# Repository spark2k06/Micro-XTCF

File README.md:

Micro XTCF (Very Low Profile) Rev1.0 ReadMe
----------------------------

8-bit ISA CompactFlash interface + Boot ROM (two separate functions that can be used individually).

Credit:
-------

Design uses schematic from Monotech-PC, which, in turn, is based on the schematic from XT-IDE Rev2 and Glitchworks:

https://github.com/monotech/XT-IDE-Deluxe
http://www.github.com/glitchwrks/xt_ide

XT-IDE Universal BIOS\
www.xtideuniversalbios.org  
www.xtideuniversalbios.org/binaries  

Use the latest working binary that includes XTIDECFG.COM (config utility), ide_xt.bin (8086/8088), ide_xtp.bin (80186/V20/V30 and up).

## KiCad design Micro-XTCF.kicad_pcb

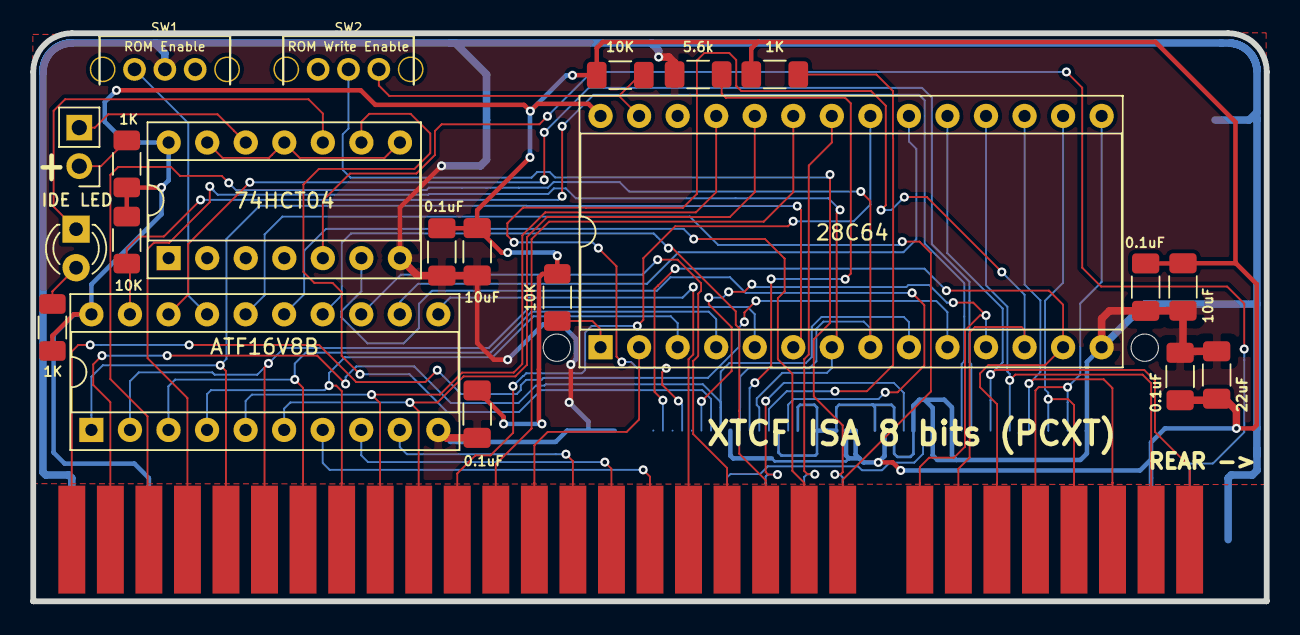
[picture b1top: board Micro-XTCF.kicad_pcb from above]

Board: 2 copper layers, 81.3 x 37.4 mm, 23 parts (1 on the bottom side), 51 nets.

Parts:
BUS1: BUSPC_DEV; ISA-8BIT-XT-CF
C1, C2, C3, C7: 0.1uF; C_1206_3216Metric_Pad1.33x1.80mm_HandSolder
C4, C5: 10uF; C_1206_3216Metric_Pad1.33x1.80mm_HandSolder
C6: 22uF; C_1206_3216Metric_Pad1.33x1.80mm_HandSolder
D1: IDE LED; LED_D3.0mm
P1: CF_CARD; Custom_CF_Slot
P2: IDE LED; PinHeader_1x02_P2.54mm_Vertical
R1: 5.6k; R_1206_3216Metric_Pad1.30x1.75mm_HandSolder
R2, R3, R4: 1K; R_1206_3216Metric_Pad1.30x1.75mm_HandSolder
R5, R6, R7: 10K; R_1206_3216Metric_Pad1.30x1.75mm_HandSolder
SW1: ROM Enable; CKCOMP-OS102011MA1QN1
SW2: ROM Write Enable; CKCOMP-OS102011MA1QN1
U1: 28C64; DIP-28_W15.24mm_Socket
U2: ATF16V8B; DIP-20_W7.62mm_Socket
U5: 74HCT04; DIP-14_W7.62mm_Socket

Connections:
/A0: BUS1.62, U1.10
/A1: BUS1.61, P1.20, U1.9
/A2: BUS1.60, P1.19, U1.8
/A3: BUS1.59, P1.18, U1.7
/A4: BUS1.58, U1.6, U2.1
/A5: BUS1.57, U1.5, U2.2
/A6: BUS1.56, U1.4, U2.3
/A7: BUS1.55, U1.3, U2.4
/A8: BUS1.54, U1.25, U2.5
/A9: BUS1.53, U1.24, U2.6
/A10: BUS1.52, U1.21
/A11: BUS1.51, U1.23
/A12: BUS1.50, U1.2
/A13: BUS1.49, U2.9
/A14: BUS1.48, U2.8
/A15: BUS1.47, U2.7
/A16: BUS1.46, U2.11
/A17: BUS1.45, U2.13
/A18: BUS1.44, U2.14
/A19: BUS1.43, U2.15
/AEN: BUS1.42, U2.16
/CF_DMARQ: P1.43, R1.1
/CF_IORDY: P1.42, R4.2
/D0: BUS1.40, P1.21, U1.11
/D1: BUS1.39, P1.22, U1.12
/D2: BUS1.38, P1.23, U1.13
/D3: BUS1.37, P1.2, U1.15
/D4: BUS1.36, P1.3, U1.16
/D5: BUS1.35, P1.4, U1.17
/D6: BUS1.34, P1.5, U1.18
/D7: BUS1.33, P1.6, U1.19
/RDY/~BUSY: R6.1, U1.1
/RSTDRV: BUS1.2, U5.5
/~CF_CS0: P1.7, U2.18
/~CF_CS1: P1.32, R5.1, U2.19
/~CF_DASP: P1.45, U5.9
/~CF_RESET: P1.41, U5.6
/~IOR: BUS1.14, P1.34
/~IOW: BUS1.13, P1.35
/~MEMR: BUS1.12, U1.22
/~MEMW: BUS1.11, SW2.2
/~ROMW: R7.2, SW2.3, U1.27
/~ROM_CS: U1.20, U2.12
/~ROM_ENABLE: SW1.1, U2.17
GND: BUS1.1, BUS1.10, BUS1.31, C1.2, C2.2, C3.2, C4.2, C5.2, C6.2, C7.2, P1.1, P1.8, P1.9, P1.10, P1.11, P1.12, P1.14, P1.15, P1.16, P1.17, P1.39, P1.50, R1.2, SW1.2, U1.14, U2.10, U5.7
unnamed: D1.1, U5.10
unnamed: D1.2, R2.2
unnamed: P2.1, R3.2
unnamed: P2.2, U5.12
unnamed: U5.8, U5.11, U5.13
VCC: BUS1.3, BUS1.29, C1.1, C2.1, C3.1, C4.1, C5.1, C6.1, C7.1, P1.13, P1.36, P1.38, P1.44, R2.1, R3.1, R4.1, R5.2, R6.2, R7.1, U1.28, U2.20, U5.14

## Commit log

2021-04-14 Rev 1.1
    Added two decouple capacitors (100nF and 22uF) on the vcc line of the cf, some cf's requires a pump when they start, thanks @arananet for the suggestion.
    Added gerbers to the github project.
2023-01-23 PCB layout sources added
2023-01-23 Revert "Update README.md"
    This reverts commit 44310f9d5a958437f32561ee5d2c6db57efdea3b.
